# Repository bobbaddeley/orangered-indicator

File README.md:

orangered-indicator
===================

A tiny edge-lit display powered by a Spark Core that connects to reddit and checks for new messages. You could modify the code to check other web sites, and the edge lit display could be any icon you want. I specifically wanted to check Reddit, so I used the envelope icon.

See http://imgur.com/a/GfWCG for a full album of the completed project.

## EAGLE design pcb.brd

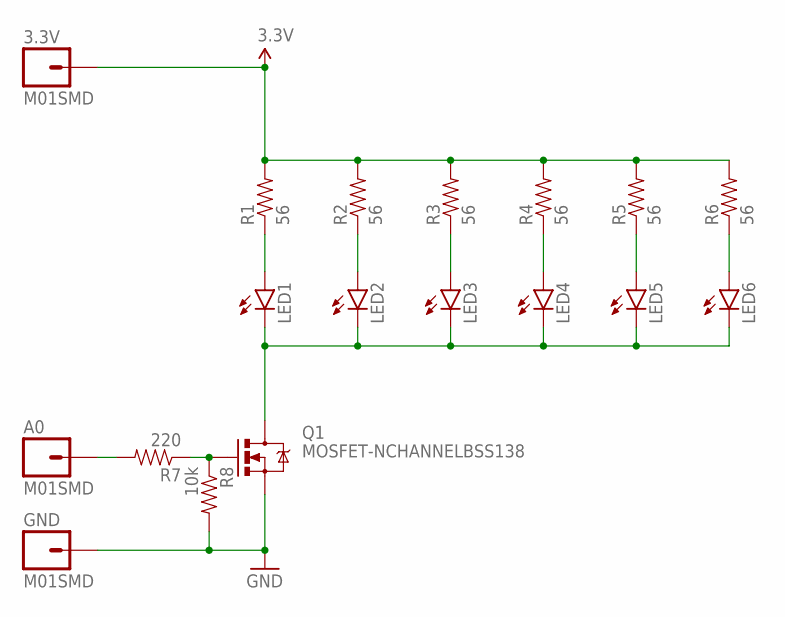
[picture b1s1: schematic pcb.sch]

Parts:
3.3V: M01SMD; LUXEON-PAD
A0: M01SMD; LUXEON-PAD
GND: M01SMD; LUXEON-PAD
LED1, LED2, LED3, LED4, LED5, LED6: LED1206; LED-1206
Q1: MOSFET-NCHANNELBSS138; SOT23-3
R1, R2, R3, R4, R5, R6: 56; 0603-RES
R7: 220; 0603-RES
R8: 10k; 0603-RES

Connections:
3.3V: 3.3V.P$1, R1.2, R2.2, R3.2, R4.2, R5.2, R6.2
GND: GND.P$1, Q1.2 (S), R8.2
unnamed: LED1.A, R1.1
unnamed: LED1.C, LED2.C, LED3.C, LED4.C, LED5.C, LED6.C, Q1.3 (D)
unnamed: A0.P$1, R7.2
unnamed: Q1.1 (G), R7.1, R8.1
unnamed: LED2.A, R2.1
unnamed: LED3.A, R3.1
unnamed: LED4.A, R4.1
unnamed: LED5.A, R5.1
unnamed: LED6.A, R6.1

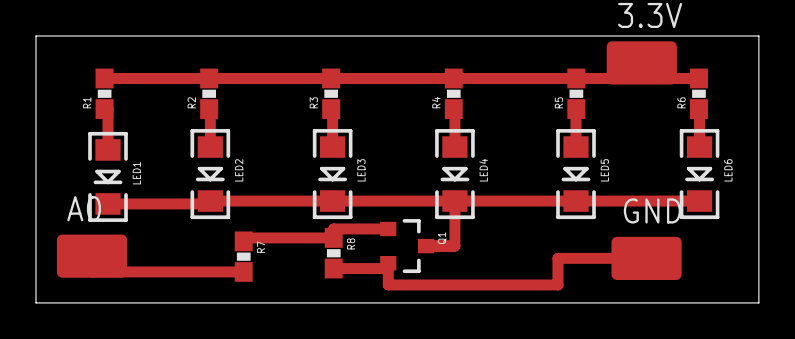
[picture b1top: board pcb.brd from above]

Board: 2 copper layers, 40.2 x 14.8 mm, 18 parts (0 on the bottom side), 11 nets.

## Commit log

2014-12-16 The code running on the Spark Core.
    Assumes the LEDs are connected through an N Channel Mosfet to A0.
2014-12-16 Adding the board.

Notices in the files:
parts and their libraries:
SparkFun-Resistors: Licensing: Creative Commons ShareAlike 4.0 International - https://creativecommons.org/licenses/by-sa/4.0
